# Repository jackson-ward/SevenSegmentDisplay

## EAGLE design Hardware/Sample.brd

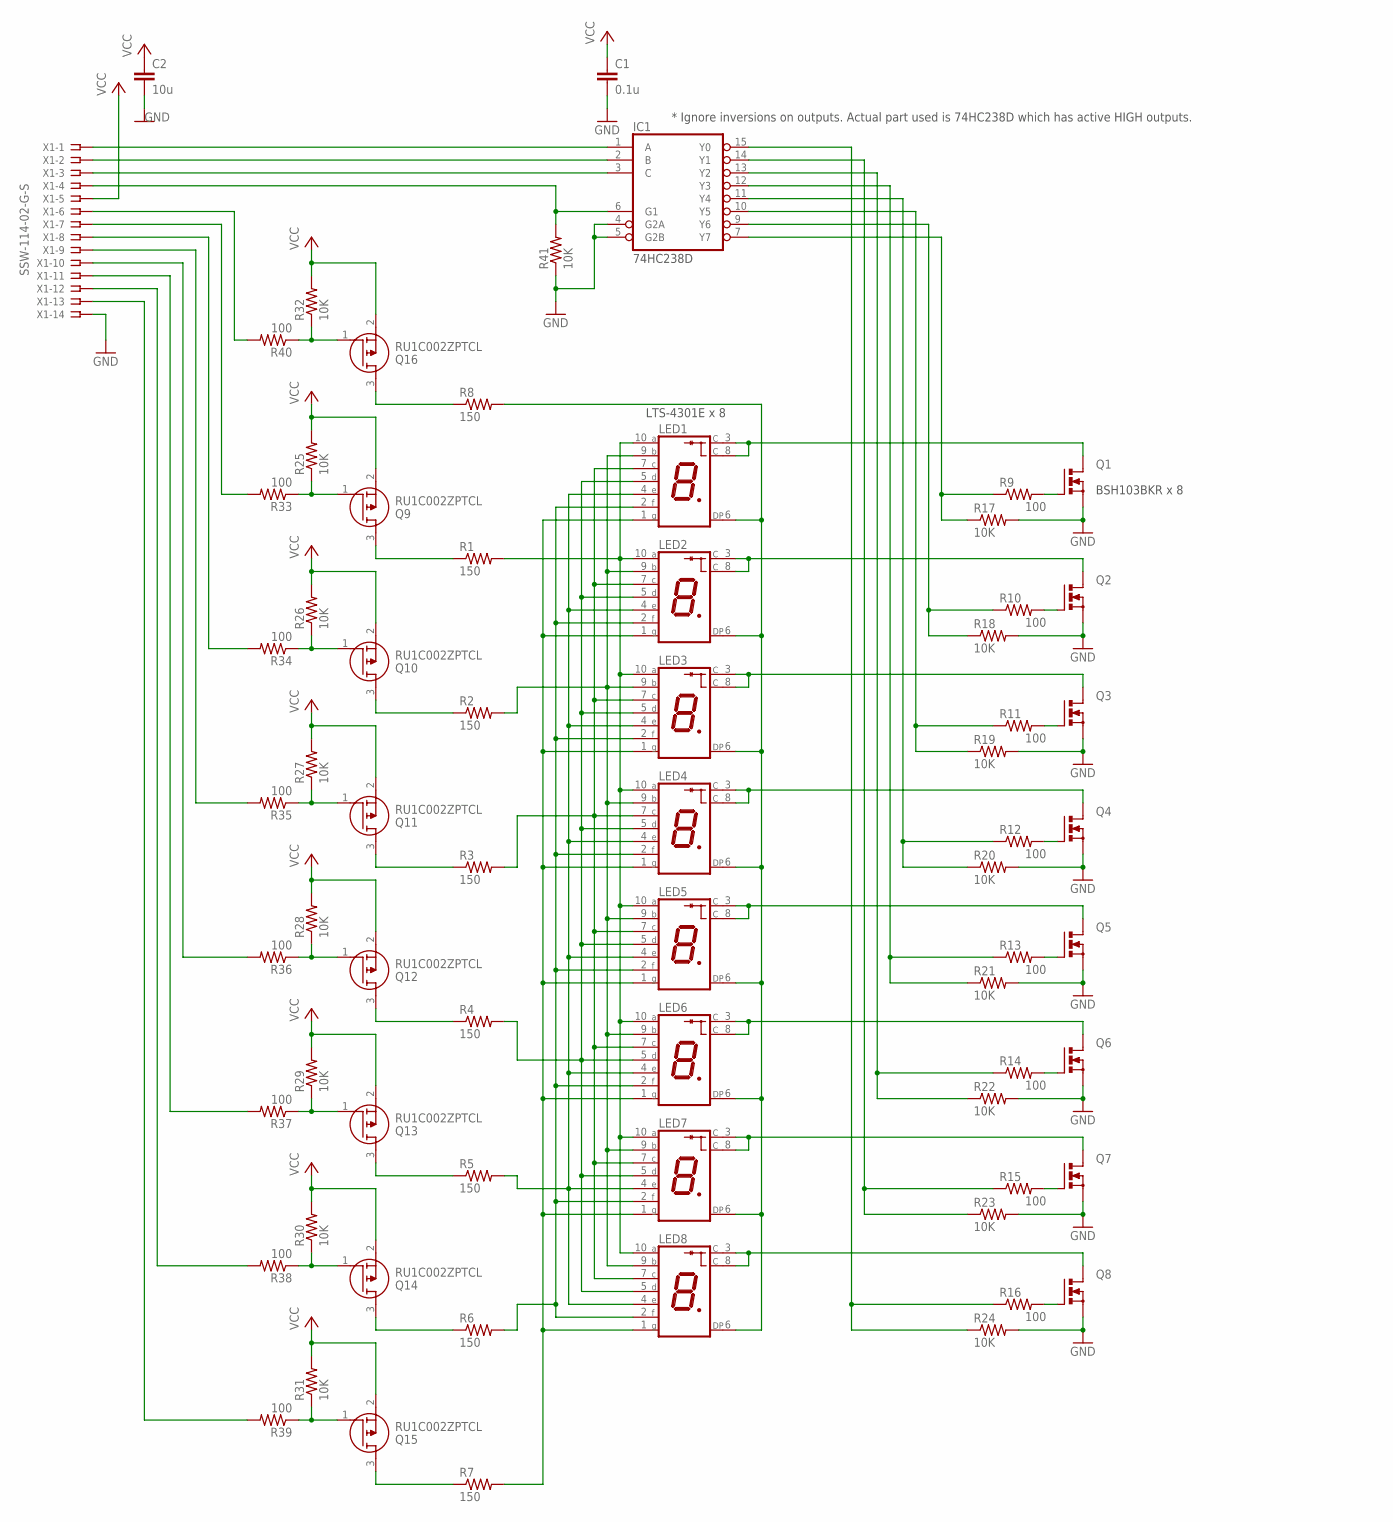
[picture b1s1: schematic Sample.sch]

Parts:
C1: 0.1u; C0805
C2: 10u; C0805
IC1: 74S138D; SO16
LED1, LED2, LED3, LED4, LED5, LED6, LED7, LED8: S4301B
Q1, Q2, Q3, Q4, Q5, Q6, Q7, Q8: N-MOSFET-SO8; SUPER-SOT3
Q9, Q10, Q11, Q12, Q13, Q14, Q15, Q16: RU1C002ZPTCL; SOTFL65P210X105-3N
R1, R2, R3, R4, R5, R6, R7, R8: 150; R0805
R9, R10, R11, R12, R13, R14, R15, R16, R33, R34, R35, R36, R37, R38, R39, R40: 100; R0805
R17, R18, R19, R20, R21, R22, R23, R24, R25, R26, R27, R28, R29, R30, R31, R32, R41: 10K; R0805
X1: SSW-114-02-G-S

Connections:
GND: C1.2, C2.2, IC1.4 (G2A), IC1.5 (G2B), IC1.8 (GND), Q1.2 (S), Q2.2 (S), Q3.2 (S), Q4.2 (S), Q5.2 (S), Q6.2 (S), Q7.2 (S), Q8.2 (S), R17.2, R18.2, R19.2, R20.2, R21.2, R22.2, R23.2, R24.2, R41.1, X1.14
LED_1_CATHODE: LED1.3 (C), LED1.8 (C), Q1.3 (D)
LED_2_CATHODE: LED2.3 (C), LED2.8 (C), Q2.3 (D)
LED_3_CATHODE: LED3.3 (C), LED3.8 (C), Q3.3 (D)
LED_4_CATHODE: LED4.3 (C), LED4.8 (C), Q4.3 (D)
LED_5_CATHODE: LED5.3 (C), LED5.8 (C), Q5.3 (D)
LED_6_CATHODE: LED6.3 (C), LED6.8 (C), Q6.3 (D)
LED_7_CATHODE: LED7.3 (C), LED7.8 (C), Q7.3 (D)
LED_8_CATHODE: LED8.3 (C), LED8.8 (C), Q8.3 (D)
unnamed: Q1.1 (G), R9.2
unnamed: Q3.1 (G), R11.2
unnamed: Q5.1 (G), R13.2
unnamed: Q6.1 (G), R14.2
unnamed: Q7.1 (G), R15.2
unnamed: Q8.1 (G), R16.2
unnamed: Q2.1 (G), R10.2
unnamed: Q4.1 (G), R12.2
unnamed: IC1.6 (G1), R41.2, X1.4
unnamed: Q9.1 (G), R25.1, R33.1
unnamed: Q10.1 (G), R26.1, R34.1
unnamed: Q14.1 (G), R30.1, R38.1
unnamed: Q11.1 (G), R27.1, R35.1
unnamed: Q13.1 (G), R29.1, R37.1
unnamed: Q12.1 (G), R28.1, R36.1
unnamed: IC1.15 (Y0), R16.1, R24.1
unnamed: IC1.14 (Y1), R15.1, R23.1
unnamed: IC1.13 (Y2), R14.1, R22.1
unnamed: IC1.12 (Y3), R13.1, R21.1
unnamed: IC1.11 (Y4), R12.1, R20.1
unnamed: IC1.10 (Y5), R11.1, R19.1
unnamed: IC1.9 (Y6), R10.1, R18.1
unnamed: IC1.7 (Y7), R9.1, R17.1
unnamed: Q16.1 (G), R32.1, R40.1
unnamed: Q15.1 (G), R31.1, R39.1
unnamed: IC1.1 (A), X1.1
unnamed: IC1.2 (B), X1.2
unnamed: IC1.3 (C), X1.3
unnamed: R40.2, X1.6
unnamed: R33.2, X1.7
unnamed: R34.2, X1.8
unnamed: R35.2, X1.9
unnamed: R36.2, X1.10
unnamed: R37.2, X1.11
unnamed: R38.2, X1.12
unnamed: R39.2, X1.13
SEGMENT_A_ANODE: LED1.10 (A), LED2.10 (A), LED3.10 (A), LED4.10 (A), LED5.10 (A), LED6.10 (A), LED7.10 (A), LED8.10 (A), R1.2
SEGMENT_A_DRAIN: Q9.3 (D), R1.1
SEGMENT_B_ANODE: LED1.9 (B), LED2.9 (B), LED3.9 (B), LED4.9 (B), LED5.9 (B), LED6.9 (B), LED7.9 (B), LED8.9 (B), R2.2
SEGMENT_B_DRAIN: Q10.3 (D), R2.1
SEGMENT_C_ANODE: LED1.7 (C), LED2.7 (C), LED3.7 (C), LED4.7 (C), LED5.7 (C), LED6.7 (C), LED7.7 (C), LED8.7 (C), R3.2
SEGMENT_C_DRAIN: Q11.3 (D), R3.1
SEGMENT_DP_ANODE: LED1.6 (DP), LED2.6 (DP), LED3.6 (DP), LED4.6 (DP), LED5.6 (DP), LED6.6 (DP), LED7.6 (DP), LED8.6 (DP), R8.2
SEGMENT_DP_DRAIN: Q16.3 (D), R8.1
SEGMENT_D_ANODE: LED1.5 (D), LED2.5 (D), LED3.5 (D), LED4.5 (D), LED5.5 (D), LED6.5 (D), LED7.5 (D), LED8.5 (D), R4.2
SEGMENT_D_DRAIN: Q12.3 (D), R4.1
SEGMENT_E_ANODE: LED1.4 (E), LED2.4 (E), LED3.4 (E), LED4.4 (E), LED5.4 (E), LED6.4 (E), LED7.4 (E), LED8.4 (E), R5.2
SEGMENT_E_DRAIN: Q13.3 (D), R5.1
SEGMENT_F_ANODE: LED1.2 (F), LED2.2 (F), LED3.2 (F), LED4.2 (F), LED5.2 (F), LED6.2 (F), LED7.2 (F), LED8.2 (F), R6.2
SEGMENT_F_DRAIN: Q14.3 (D), R6.1
SEGMENT_G_ANODE: LED1.1 (G), LED2.1 (G), LED3.1 (G), LED4.1 (G), LED5.1 (G), LED6.1 (G), LED7.1 (G), LED8.1 (G), R7.2
SEGMENT_G_DRAIN: Q15.3 (D), R7.1
VCC: C1.1, C2.1, IC1.16 (VCC), Q9.2 (S), Q10.2 (S), Q11.2 (S), Q12.2 (S), Q13.2 (S), Q14.2 (S), Q15.2 (S), Q16.2 (S), R25.2, R26.2, R27.2, R28.2, R29.2, R30.2, R31.2, R32.2, X1.5

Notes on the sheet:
* Ignore inversions on outputs. Actual part used is 74HC238D which has active HIGH outputs.
74HC238D
BSH103BKR x 8
LTS-4301E x 8

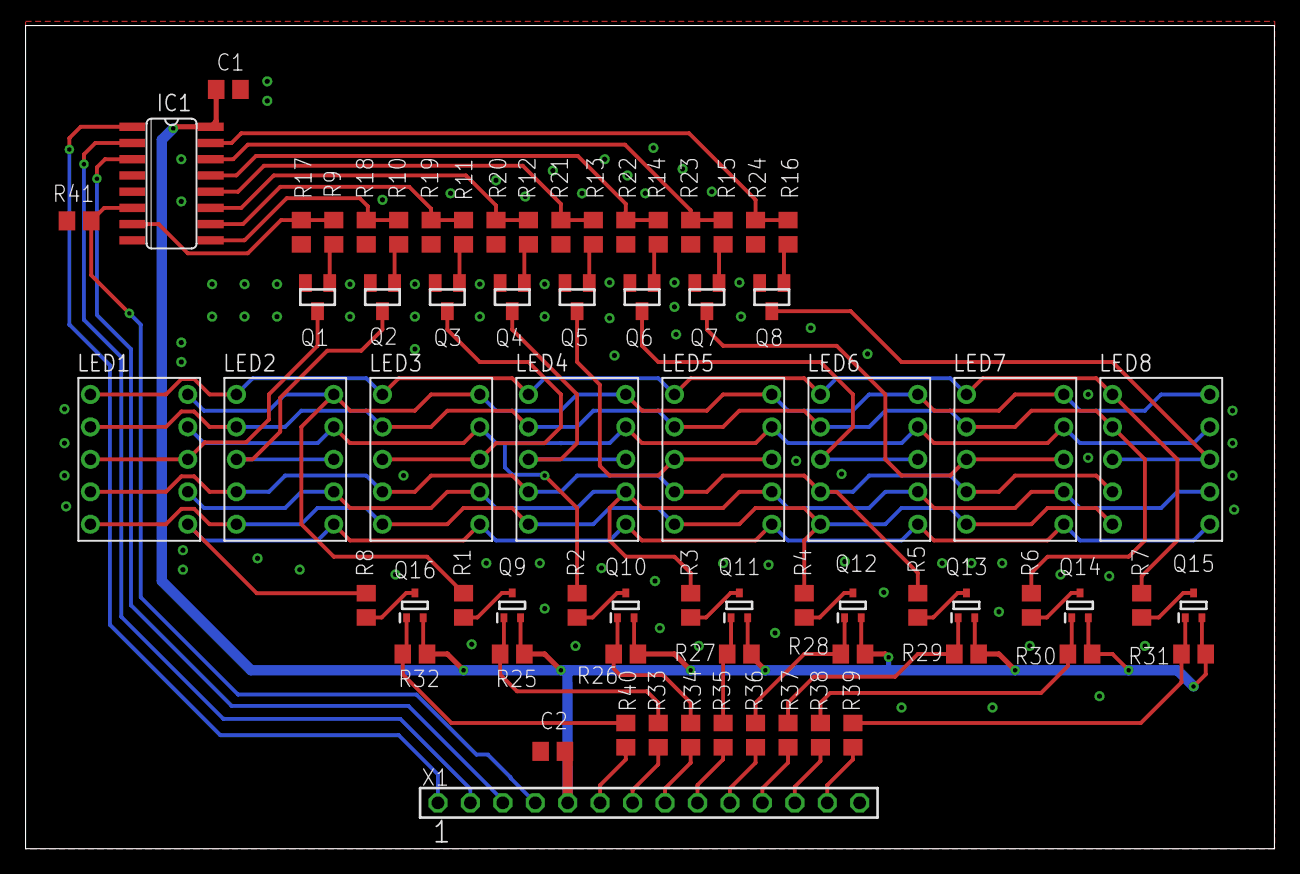
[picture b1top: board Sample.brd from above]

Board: 2 copper layers, 97.8 x 64.4 mm, 69 parts (0 on the bottom side), 62 nets.

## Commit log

2025-05-19 removed accidental shortcut link
